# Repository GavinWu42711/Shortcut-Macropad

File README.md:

# Shortcut-Macropad
Personal macropad for common shortcuts that I use often with 6 keys (cut, copy, paste, change tabs x2, and save), an oled screen and a mini led for status. Made for Blueprint

# Motivation
Personally, this is my first experience with this kind of hardware event and a little out of my comfort zone. This projects serves as an introduction to CAD, a little bit of circuit python, journaling, and making and designing PCB's.

# Pictures of Completed product and parts

# Picture of schmeatic

# Pictures of PCB

# Specifications
BOM:
  - 6x Cherry MX Switches
  - 1x SK6812 MINI Leds
  - 1x XIAO RP2040
  - 6x Blank DSA Keycaps
  - 1x 0.91 in. I2C OLED Display (128 x 32, SSD 1306)
  - 4x M3x16mm screws

Other:
  - KMK Firmware
  - Top & Bottom of case (3D printed)

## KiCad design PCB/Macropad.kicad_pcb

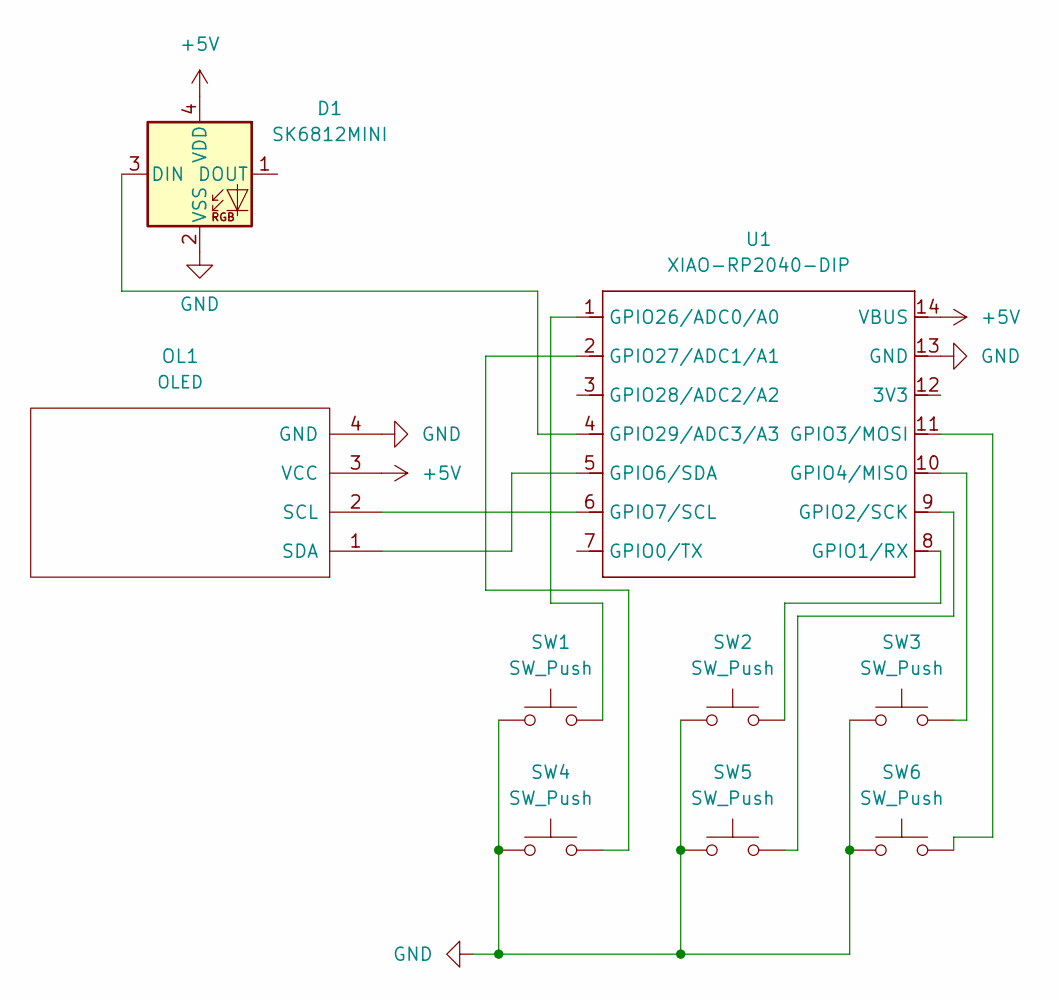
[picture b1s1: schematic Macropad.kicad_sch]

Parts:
D1: SK6812MINI; LED_SK6812MINI_PLCC4_3.5x3.5mm_P1.75mm
OL1: OLED
SW1, SW2, SW3, SW4, SW5, SW6: SW_Push; SW_Cherry_MX_1.00u_PCB
U1: XIAO-RP2040-DIP

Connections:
+5V: D1.4 (VDD), OL1.3 (VCC), U1.14 (VBUS)
GND: D1.2 (VSS), OL1.4 (GND), SW1.1, SW2.1, SW3.1, SW4.1, SW5.1, SW6.1, U1.13 (GND)
unnamed: D1.3 (DIN), U1.4 (GPIO29/ADC3/A3)
unnamed: OL1.2 (SCL), U1.6 (GPIO7/SCL)
unnamed: OL1.1 (SDA), U1.5 (GPIO6/SDA)
unnamed: SW2.2, U1.8 (GPIO1/RX)
unnamed: SW5.2, U1.9 (GPIO2/SCK)
unnamed: SW6.2, U1.11 (GPIO3/MOSI)
unnamed: SW3.2, U1.10 (GPIO4/MISO)
unnamed: SW1.2, U1.1 (GPIO26/ADC0/A0)
unnamed: SW4.2, U1.2 (GPIO27/ADC1/A1)

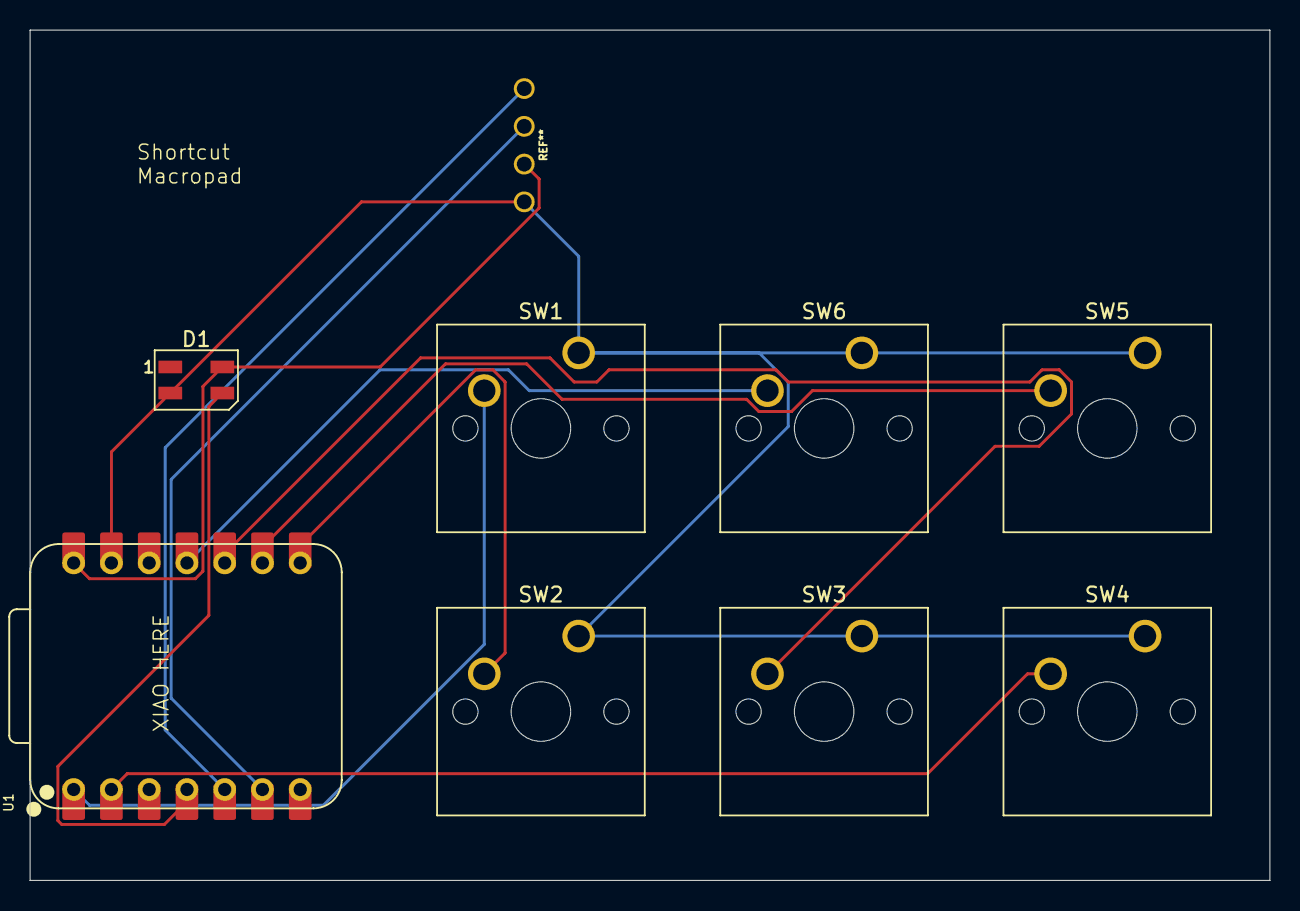
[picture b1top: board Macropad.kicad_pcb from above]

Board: 2 copper layers, 83.4 x 57.2 mm, 9 parts (0 on the bottom side), 11 nets.

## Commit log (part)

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2026-01-02 Files
    Adding in all the files
2026-01-04 Update README.md
    BOM
2026-01-04 Update README.md
    motivation
